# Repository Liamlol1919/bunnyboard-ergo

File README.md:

# bunnyboard
this is a custom stenography keyboard i built with [hackclub's onboard grant](https://onboard.hackclub.com)!

## ergo variant (working copy)
This tree contains a transformed variant of the original bunnyboard: the same
electrical design (pads, nets, matrix, diodes, Pico pinout are bit-identical),
only the (x, y, rot) values of the 28 switches, 28 diodes and the Pico are
changed. Generated by `tools/ergo_transform.py`, routed by `tools/route.sh`.

### pitch: 19 mm grid, not measured fingertip distance
Two candidates were compared (`tools/vergleich_pitch.py`):

| | Pinky-Index | Ring-Middle cap gap |
|---|---|---|
| V1 fingertip (Wacom dx) | 56.0 mm | **0.5 mm** |
| V2 19 mm switch grid | 57.0 mm | **4.0 mm** |

V1 is rejected: a 0.5 mm gap between the Ring and Middle caps means a
mis-hit presses two keys at once. The measured fingertip spacing is narrower
than the switch grid because the hand rests spread out; the grid has to
follow the switch pitch (Choc = 19 mm), not the fingertips. Stagger (dy) is
taken from the measurement - that is the actual ergonomic effect.

### middle gap: 120 mm
The two middle fingers sit 120 mm apart (measured: 84-92 mm). The extra width
pays for the Pico: it is 23.1 mm wide and sits between the asterisk columns,
which additionally need 2 x 9.125 mm for their diode offsets plus clearance
-> 42.1 mm between the asterisk caps. At 96 mm the asterisks were only 28 mm
apart and the Pico overlapped S6/S17.

### thumb rotation: 3 degrees
The 3 thumb keys per hand are rotated so they face the thumb instead of
standing axis-parallel. Left hand +3, right hand -3.
NOTE: the Choc footprint is NOT mirror-symmetric - all six thumb switches
have the same pad axis (22.78 deg) in the source board. The sign therefore
cannot be derived from "mirror the left hand"; it is set per hand and must
be verified visually on the render. The angle is limited by the caps, not by taste:
a Choc-1u cap is 17.5 x 16.5 mm (the 15 mm used in the first calculation was
too optimistic), and rotating a cap by a widens its bounding box to
17.5*(cos a + sin a). S23 and S24 are 19.36 mm apart:

| angle | cap bbox | gap S23-S24 |
|---|---|---|
| 0 | 17.50 mm | +1.86 mm |
| **3 (chosen)** | 18.39 mm | **+0.97 mm** |
| 6 | 19.23 mm | +0.13 mm |
| 12 | 20.76 mm | -1.40 mm overlap |

DRC does not catch cap collisions - it only checks copper. At 12 degrees the
two caps physically touch, which only shows up during assembly.

### chamfer: outer corners only
The T-outline transition from the bank to the tongue is a concave corner.
A chamfer there cuts away material the corner needs. Fase is applied only to
the convex corners: the 4 bank corners and the 2 tongue ends.

### outline
`Edge.Cuts` is rebuilt as a T shape from the actual key extents, not from the
raw bounding box of the source board. Margin is 4 mm from the keycap edge
(previously 12.5 mm as in bunnys original): a board that lies flat does not
need more, and JLCPCB only requires 0.2 mm copper-to-edge - the smallest
actual copper-to-edge distance here is 1.62 mm.

The copper logo (`G***`) was removed: it is decoration and cost board area.

| | before | after |
|---|---|---|
| Board | 253.6 x 114.2 mm | **236.6 x 97.2 mm** |
| Margin (cap edge to board edge) | 10.5-12.5 mm | 4.0 mm |
| Copper to edge (min) | - | 1.62 mm |

## specs and other stuff
- powered by a Raspberry Pi Pico
- runs QMK firmware
- uses Kailh choc v1 switches

## keyboard layout
the keyboard layout is almost identical to "The Uni" stenokeyboard, except for the top-left key (which is a "#" instead of an "S").
```
.------------------------------------------------.
| # | T | P | H | * |    | * | F | P | L | T | D |
| S | K | W | R | * |    | * | R | B | G | S | Z |
'-------| # | A | O |    | E | U | # |-----------'
        '----------------------------'
```
## how to get this keyboard
1. get the pcb and solder the components
   - PCB gerber located at "/keyboard/production/gerber.zip
   - components needed:
     - 28 kailh v1 choc switches + keycaps (i got mine for $32 USD at chosfox!)
     - raspberry pi pico + header pins
     - 28 1N4148 Diodes (you can choose to have them soldered on if you're using JLCPCB)
2. install the QMK firmware (read [here](https://docs.qmk.fm/newbs_flashing) for more info)
3. install/setup plover (see a tutorial [here](https://docs.stenokeyboards.com/guides/))
   - select "Gemini PR" as your keyboard
   - set output to "Enabled"
4. profit

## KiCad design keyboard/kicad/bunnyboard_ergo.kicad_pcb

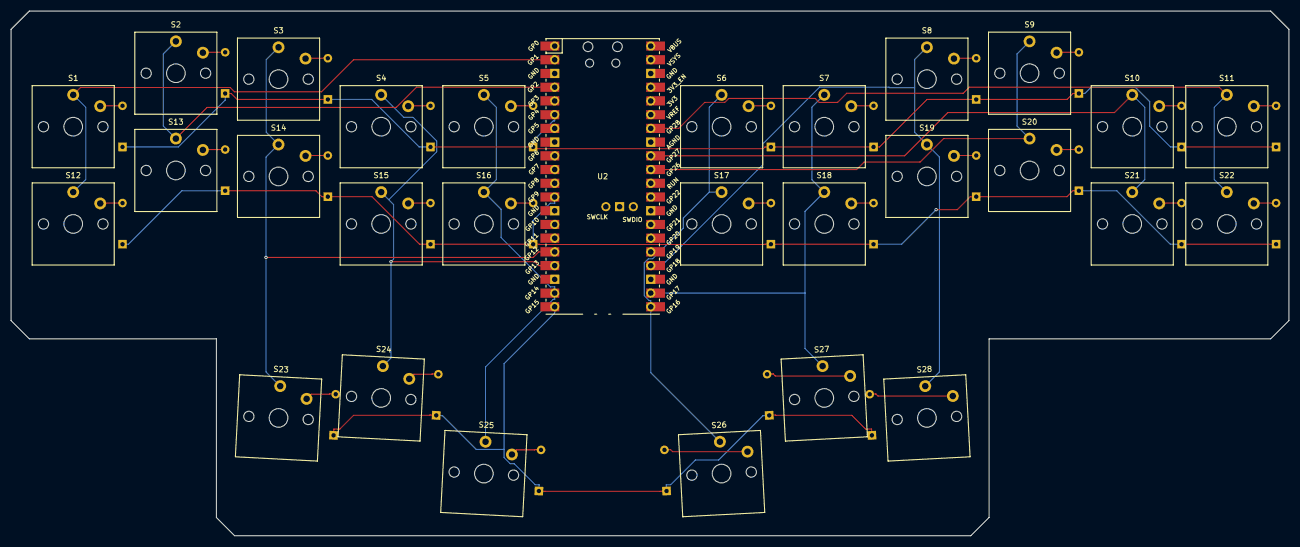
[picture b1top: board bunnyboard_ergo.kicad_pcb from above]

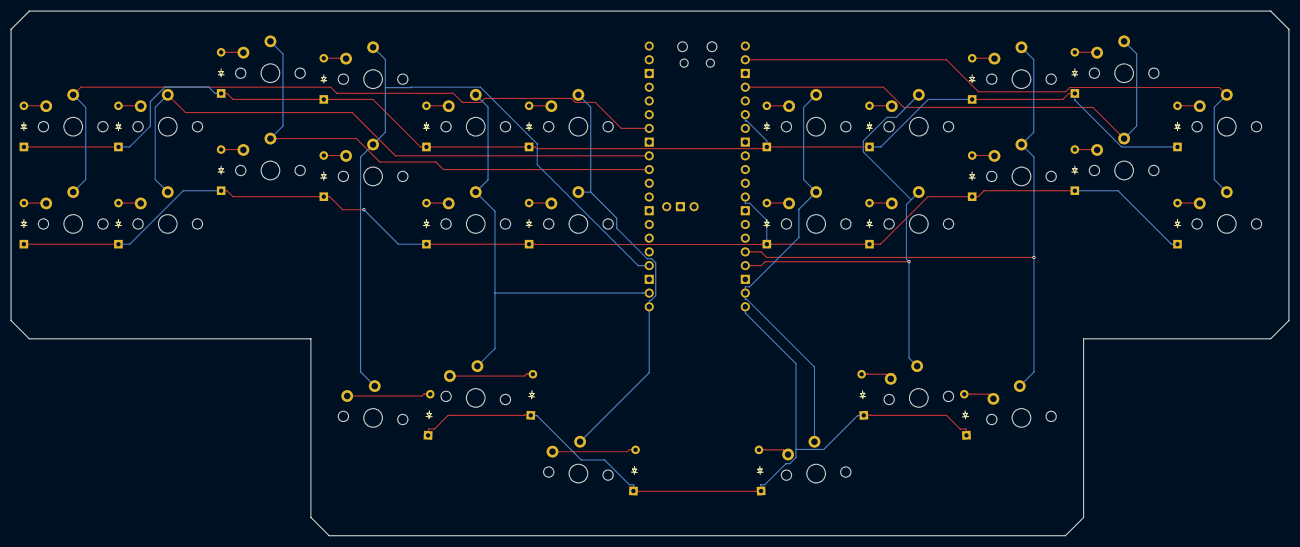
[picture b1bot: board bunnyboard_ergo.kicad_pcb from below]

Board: 2 copper layers, 236.5 x 97.1 mm, 57 parts (28 on the bottom side), 42 nets.

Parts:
D1, D2, D3, D4, D5, D6, D7, D8, D9, D10, D11, D12, D13, D14, D15, D16, D17, D18, D19, D20, D21, D22, D23, D24, D25, D26, D27, D28: D; Diode_DO-35
S1, S2, S3, S4, S5, S6, S7, S8, S9, S10, S11, S12, S13, S14, S15, S16, S17, S18, S19, S20, S21, S22, S23, S24, S25, S26, S27, S28: Keyswitch; Choc_V1_1.00u
U2: Pico; RPi_PicoW_SMD_TH

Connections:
Column 0: S1.1, S12.1, U2.2 (GPIO1)
Column 1: S2.1, S13.1, U2.4 (GPIO2)
Column 2: S3.1, S14.1, S23.1, U2.16 (GPIO12)
Column 3: S4.1, S15.1, S24.1, U2.17 (GPIO13)
Column 4: S5.1, S16.1, S25.1, U2.19 (GPIO14)
Column 5: S6.1, S17.1, S26.1, U2.21 (GPIO16)
Column 6: S7.1, S18.1, S27.1, U2.22 (GPIO17)
Column 7: S8.1, S19.1, S28.1, U2.24 (GPIO18)
Column 8: S9.1, S20.1, U2.31 (GPIO26_ADC0)
Column 9: S10.1, S21.1, U2.32 (GPIO27_ADC1)
Column 10: S11.1, S22.1, U2.34 (GPIO28_ADC2)
unnamed: D1.2 (A), S1.2
unnamed: D2.2 (A), S2.2
unnamed: D3.2 (A), S3.2
unnamed: D4.2 (A), S4.2
unnamed: D5.2 (A), S5.2
unnamed: D6.2 (A), S6.2
unnamed: D7.2 (A), S7.2
unnamed: D8.2 (A), S8.2
unnamed: D9.2 (A), S9.2
unnamed: D10.2 (A), S10.2
unnamed: D11.2 (A), S11.2
unnamed: D12.2 (A), S12.2
unnamed: D13.2 (A), S13.2
unnamed: D14.2 (A), S14.2
unnamed: D15.2 (A), S15.2
unnamed: D16.2 (A), S16.2
unnamed: D17.2 (A), S17.2
unnamed: D18.2 (A), S18.2
unnamed: D19.2 (A), S19.2
unnamed: D20.2 (A), S20.2
unnamed: D21.2 (A), S21.2
unnamed: D22.2 (A), S22.2
unnamed: D23.2 (A), S23.2
unnamed: D24.2 (A), S24.2
unnamed: D25.2 (A), S25.2
unnamed: D26.2 (A), S26.2
unnamed: D27.2 (A), S27.2
unnamed: D28.2 (A), S28.2
Row 0: D1.1 (K), D2.1 (K), D3.1 (K), D4.1 (K), D5.1 (K), D6.1 (K), D7.1 (K), D8.1 (K), D9.1 (K), D10.1 (K), D11.1 (K), U2.6 (GPIO4)
Row 1: D12.1 (K), D13.1 (K), D14.1 (K), D15.1 (K), D16.1 (K), D17.1 (K), D18.1 (K), D19.1 (K), D20.1 (K), D21.1 (K), D22.1 (K), U2.12 (GPIO9)
Row 2: D23.1 (K), D24.1 (K), D25.1 (K), D26.1 (K), D27.1 (K), D28.1 (K), U2.20 (GPIO15)
